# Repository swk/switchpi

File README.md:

switchpi
========

Turning a RaspberryPI into VoIP Phone, and Small SoftSwitch with some extra bells and whistles

(C)2013-2019 Ken Rice <krice )at( freeswitch dot org> 

All Souce code is MPL1.1 License.

All Hardware is designs are licensed under the Creative Commons Attribution-NonCommercial-ShareAlike 3.0 Unported License.
To view a copy of this license, visit http://creativecommons.org/licenses/by-nc-sa/3.0/. 

** So, some group in China is trying to steal my project name. Not very Nice of them. Found this by looking for SwitchPi PBX, Well you found SwitchPI the original. Not the Rip Off **

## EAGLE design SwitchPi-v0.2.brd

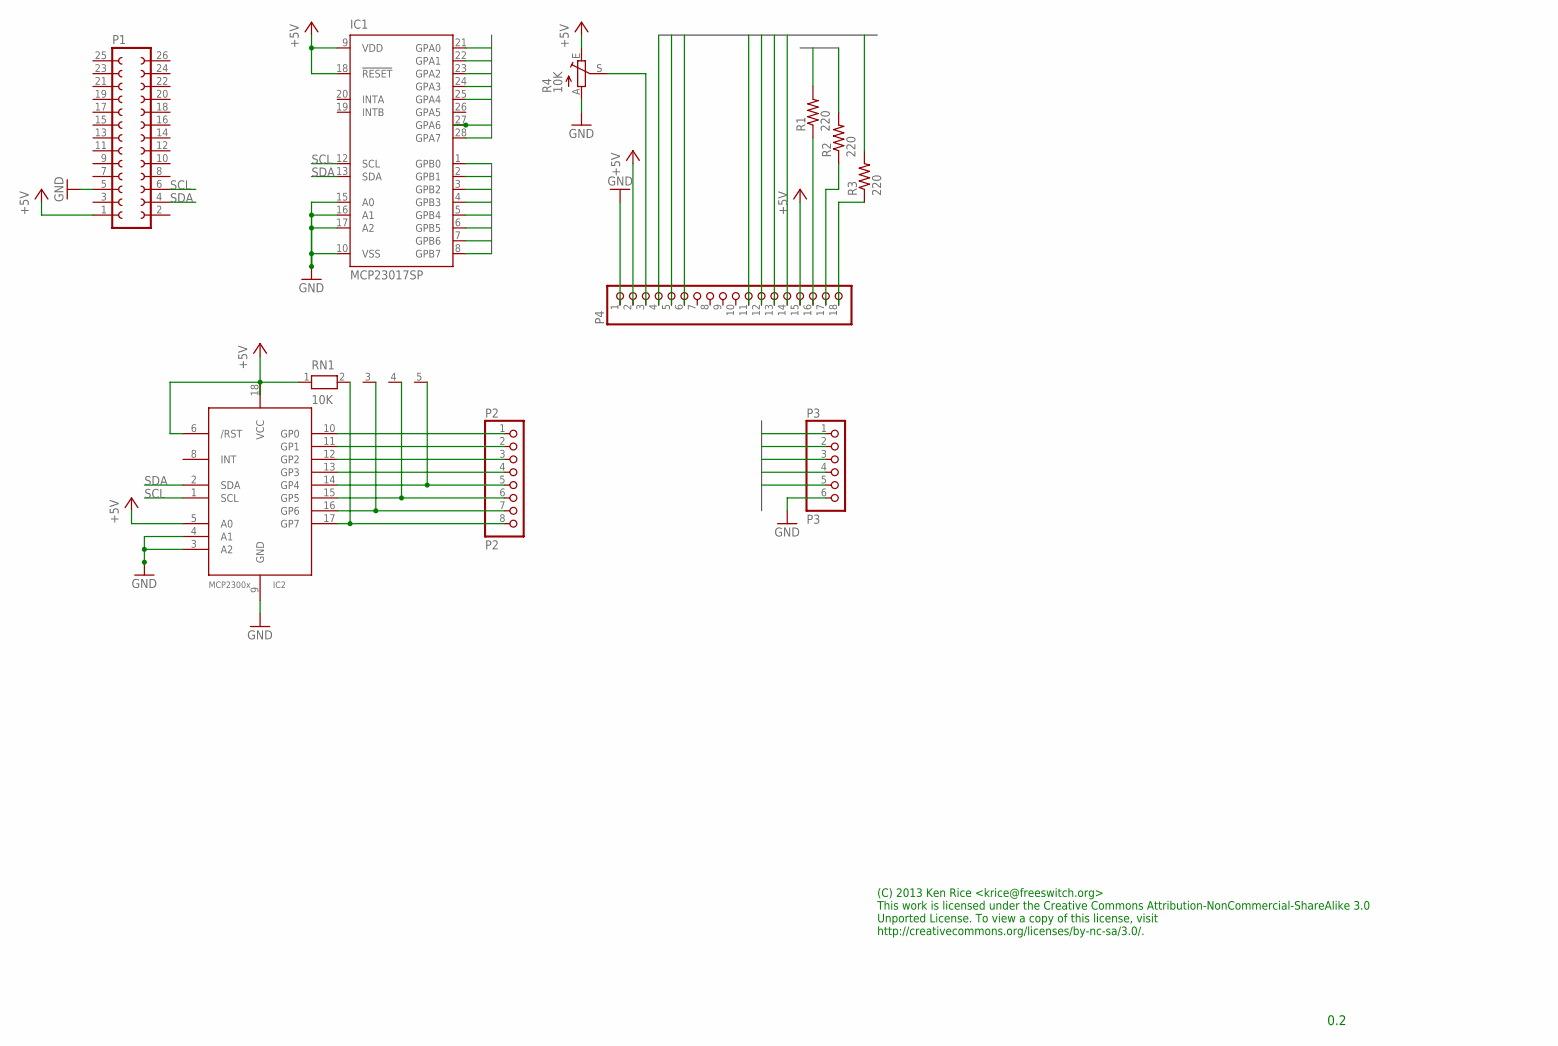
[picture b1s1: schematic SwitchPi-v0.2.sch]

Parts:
IC1: MCP23017SP; DIL28-3
IC2: MCP2300X/P; DIL18
P1: FE13-2
P2: P2; 1X08-BIG
P3: P3; 1X06
P4: PINHD-1X18-BIG; 1X18-BIG
R1, R2, R3: 220; 0207/10
R4: 10K; CA6V
RN1: 10K; RN-5

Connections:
+5V: IC1.9 (VDD), IC1.18 (!RESET), IC2.5 (A0), IC2.6 (/RST), IC2.18 (VCC), P1.1, P4.2, P4.15, R4.E, RN1.1
GND: IC1.10 (VSS), IC1.15 (A0), IC1.16 (A1), IC1.17 (A2), IC2.3 (A2), IC2.4 (A1), IC2.9 (GND), P1.5, P3.6, P4.1, R4.A
GPA0: IC1.21 (GPA0), P3.1
GPA1: IC1.22 (GPA1), P3.2
GPA2: IC1.23 (GPA2), P3.3
GPA3: IC1.24 (GPA3), P3.4
GPA4: IC1.25 (GPA4), P3.5
GPA6: IC1.27 (GPA6), R1.2
GPA7: IC1.28 (GPA7), R2.2
GPB0: IC1.1 (GPB0), R3.2
GPB1: IC1.2 (GPB1), P4.14
GPB2: IC1.3 (GPB2), P4.13
GPB3: IC1.4 (GPB3), P4.12
GPB4: IC1.5 (GPB4), P4.11
GPB5: IC1.6 (GPB5), P4.6
GPB6: IC1.7 (GPB6), P4.5
GPB7: IC1.8 (GPB7), P4.4
unnamed: IC2.10 (GP0), P2.1
unnamed: IC2.11 (GP1), P2.2
unnamed: P4.3, R4.S
unnamed: IC2.12 (GP2), P2.3
unnamed: P4.16, R1.1
unnamed: IC2.13 (GP3), P2.4
unnamed: IC2.14 (GP4), P2.5, RN1.5
unnamed: IC2.15 (GP5), P2.6, RN1.4
unnamed: IC2.16 (GP6), P2.7, RN1.3
unnamed: IC2.17 (GP7), P2.8, RN1.2
unnamed: P4.17, R2.1
unnamed: P4.18, R3.1
SCL: IC1.12 (SCL), IC2.1 (SCL), P1.6
SDA: IC1.13 (SDA), IC2.2 (SDA), P1.4

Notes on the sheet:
(C) 2013 Ken Rice <krice@freeswitch.org> This work is licensed under the Creative Commons Attribution-NonCommercial-ShareAlike 3.0 Unported License. To view a copy of this license, visit http://creativecommons.org/licenses/by-nc-sa/3.0/.
0.2

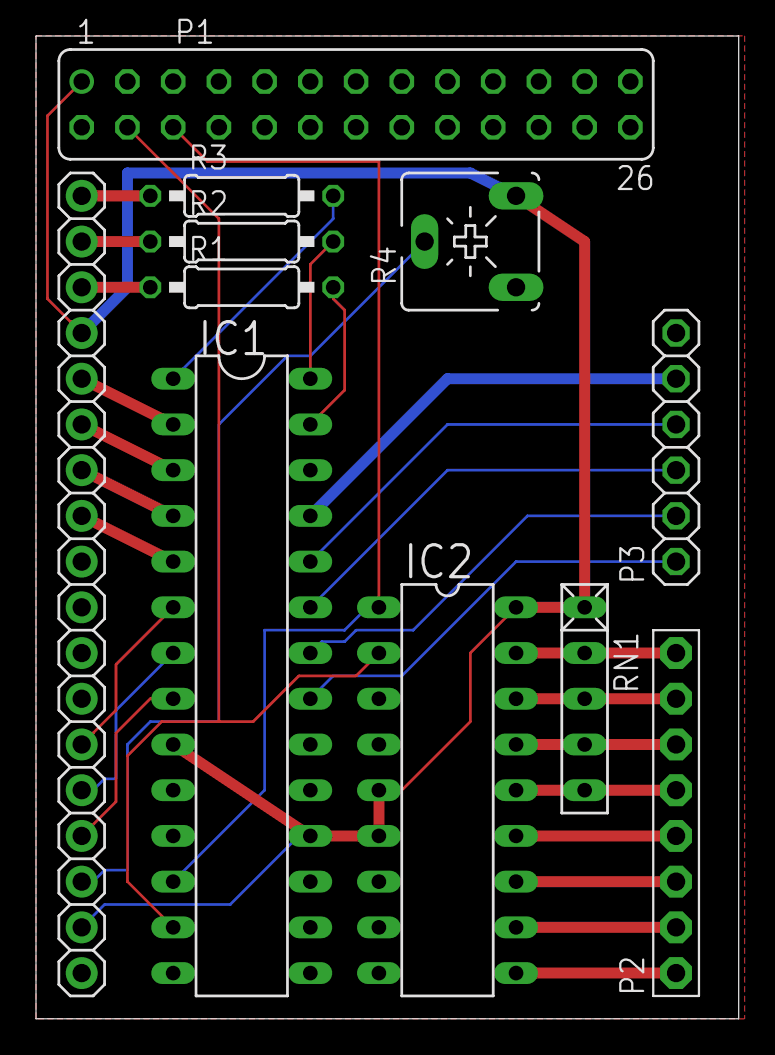
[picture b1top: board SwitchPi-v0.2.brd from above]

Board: 2 copper layers, 39.0 x 54.6 mm, 11 parts (0 on the bottom side), 31 nets.

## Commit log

2013-02-13 Initial Import
2013-02-13 small changes to board layout to clean up some traces
2013-02-21 initial commit of example C keypad driver. this keypad driver requires the use of wiringPi
2013-02-25 add another board concept. I really need an experienced EE to look at these
2013-02-25 hmmm maybe... anyone wanna tell me if this is bad? lol
2013-02-28 doc tweak
2013-03-14 add mod_switchpi, and add switch hook code to keypad test program
2019-07-24 update copyright statements because the ripoff artists are about
